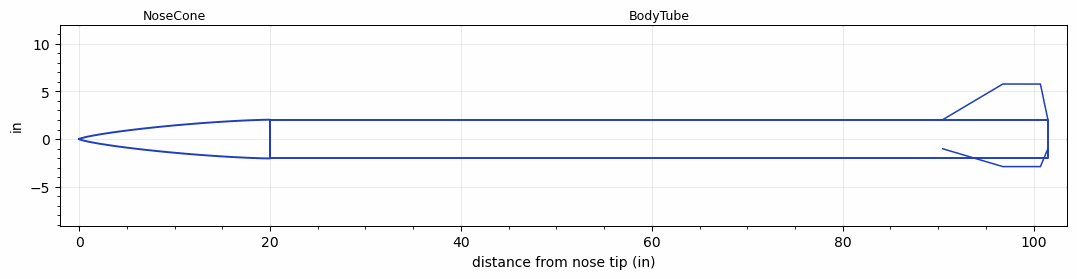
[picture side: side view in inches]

<RASAeroDocument>
 <FileVersion>2</FileVersion>
 <RocketDesign>
  <NoseCone>
   <Length>20</Length>
   <Diameter>4.0551</Diameter>
   <Shape>Von Karman Ogive</Shape>
   <Location>0</Location>
  </NoseCone>
  <BodyTube>
   <Length>81.496</Length>
   <Diameter>4.0551</Diameter>
   <RailGuideDiameter>0.5</RailGuideDiameter>
   <RailGuideHeight>0.5</RailGuideHeight>
   <Location>20</Location>
   <Fin>
    <Count>3</Count>
    <Chord>11.0236</Chord>
    <Span>3.7401</Span>
    <SweepDistance>6.2992</SweepDistance>
    <TipChord>3.937</TipChord>
    <Thickness>0.125</Thickness>
    <Location>11.0236</Location>
    <AirfoilSection>Square</AirfoilSection>
   </Fin>
  </BodyTube>
  <Surface>Smooth Paint</Surface>
  <ModifiedBarrowman>False</ModifiedBarrowman>
  <Turbulence>False</Turbulence>
  <UseBooster1>False</UseBooster1>
  <UseBooster2>False</UseBooster2>
 </RocketDesign>
 <LaunchSite>
  <Altitude>4320</Altitude>
  <Pressure>29.91</Pressure>
  <RodAngle>5</RodAngle>
  <RodLength>18</RodLength>
  <Temperature>77</Temperature>
  <WindSpeed>8.33</WindSpeed>
 </LaunchSite>
 <Recovery>
  <Altitude1>1000</Altitude1>
  <Altitude2>1000</Altitude2>
  <DeviceType1>None</DeviceType1>
  <DeviceType2>None</DeviceType2>
  <Event1>False</Event1>
  <Event2>False</Event2>
  <Size1>1</Size1>
  <Size2>1</Size2>
  <EventType1>None</EventType1>
  <EventType2>None</EventType2>
  <CD1>1.33</CD1>
  <CD2>1.33</CD2>
 </Recovery>
 <SimulationList>
  <Simulation>
   <SustainerEngine>M1830-CS  (CTI)</SustainerEngine>
   <SustainerLaunchWt>40.06</SustainerLaunchWt>
   <SustainerNozzleDiameter>2</SustainerNozzleDiameter>
   <SustainerCG>62.59</SustainerCG>
   <SustainerIgnitionDelay>0</SustainerIgnitionDelay>
   <Booster1SeparationDelay>0</Booster1SeparationDelay>
   <Booster1IgnitionDelay>0</Booster1IgnitionDelay>
   <IncludeBooster1>False</IncludeBooster1>
   <Booster2Delay>0</Booster2Delay>
   <IncludeBooster2>False</IncludeBooster2>
   <TimetoApogee>25.68049</TimetoApogee>
   <MaxAltitude>10876.63</MaxAltitude>
   <MaxVelocity>963.6298</MaxVelocity>
  </Simulation>
 </SimulationList>
</RASAeroDocument>
